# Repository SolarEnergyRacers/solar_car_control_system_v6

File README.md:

# solar_car_control_system_v6

[solarenergyracers.ch](https://www.solarenergyracers.ch) - control system (multi controller based control system for SER v6 solar car)

## Folder Structure

```Text
.
├── AC
│   ├── CMakeLists.txt
│   ├── dependencies.lock
│   ├── lib
│   │   ├── CarControl
│   │   ├── CarState
│   │   ├── CmdHandler
│   │   ├── ConfigReader
│   │   ├── Console
│   │   ├── definitions.h
│   │   ├── Display
│   │   ├── DisplayValue
│   │   ├── DriverDisplay
│   │   ├── EngineerDisplay
│   │   ├── GPIO
│   │   ├── interfaces
│   │   ├── LocalFunctionsAndDevices.h
│   │   ├── OneWireBus
│   │   ├── placeholder.txt
│   │   ├── SDCard
│   │   └── SPIBus
│   ├── platformio.ini
│   ├── sdkconfig
│   ├── sdkconfig.defaults
│   ├── sdkconfig.esp32dev
│   ├── sdkconfig.esp32dev-linux
│   ├── sdkconfig.esp32dev-windows
│   ├── ser_v6_AC.code-workspace
│   ├── src
│   │   ├── CMakeLists.txt
│   │   └── main.cpp
│   └── upload_no_build.py
├── archive_logs.py
├── data
├── datasheets
├── DC
│   ├── CMakeLists.txt
│   ├── dependencies.lock
│   ├── lib
│   │   ├── ADC
│   │   ├── CAN
│   │   ├── CarControl
│   │   ├── CarState
│   │   ├── CmdHandler
│   │   ├── ConstSpeed
│   │   ├── DAC
│   │   ├── definitions.h
│   │   ├── GPIO
│   │   ├── IOExt
│   │   ├── LocalFunctionsAndDevices.h
│   │   ├── OneWireBus
│   │   └── SPIBus
│   ├── platformio.ini
│   ├── sdkconfig
│   ├── sdkconfig.defaults
│   ├── sdkconfig.esp32dev
│   ├── sdkconfig.esp32dev-linux
│   ├── sdkconfig.esp32dev-windows
│   ├── ser_v6_DC.code-workspace
│   ├── src
│   │   ├── CMakeLists.txt
│   │   └── main.cpp
│   └── upload_no_build.py
├── PCBs
│   ├── AuxController
│   ├── ChassisBoard
│   ├── DriveController
│   ├── PDFs_Images
│   └── SwitchBoard
├── docs
├── drafts
├── extras
├── fixes_for_librarys
│   ├── core.h
│   ├── fixes.md
│   └── rtc.h
├── lib_common
│   ├── CAN
│   ├── Console
│   ├── Helper
│   ├── I2CBus
│   ├── include
│   ├── interfaces
│   ├── RTC
│   ├── Serial
│   └── System
├── platformio.txt
├── README.md
├── reset_usb_numbering.py
└── start-vscode-for-AC-DC-workspace.py

```

## Drafts

- 
- 
- 
- 
- 

## Docs

- [Signal Flows](docs/SignalFlows.md)
- [CAN Signal](docs/SignalFlows_CAN-Definitions.md)

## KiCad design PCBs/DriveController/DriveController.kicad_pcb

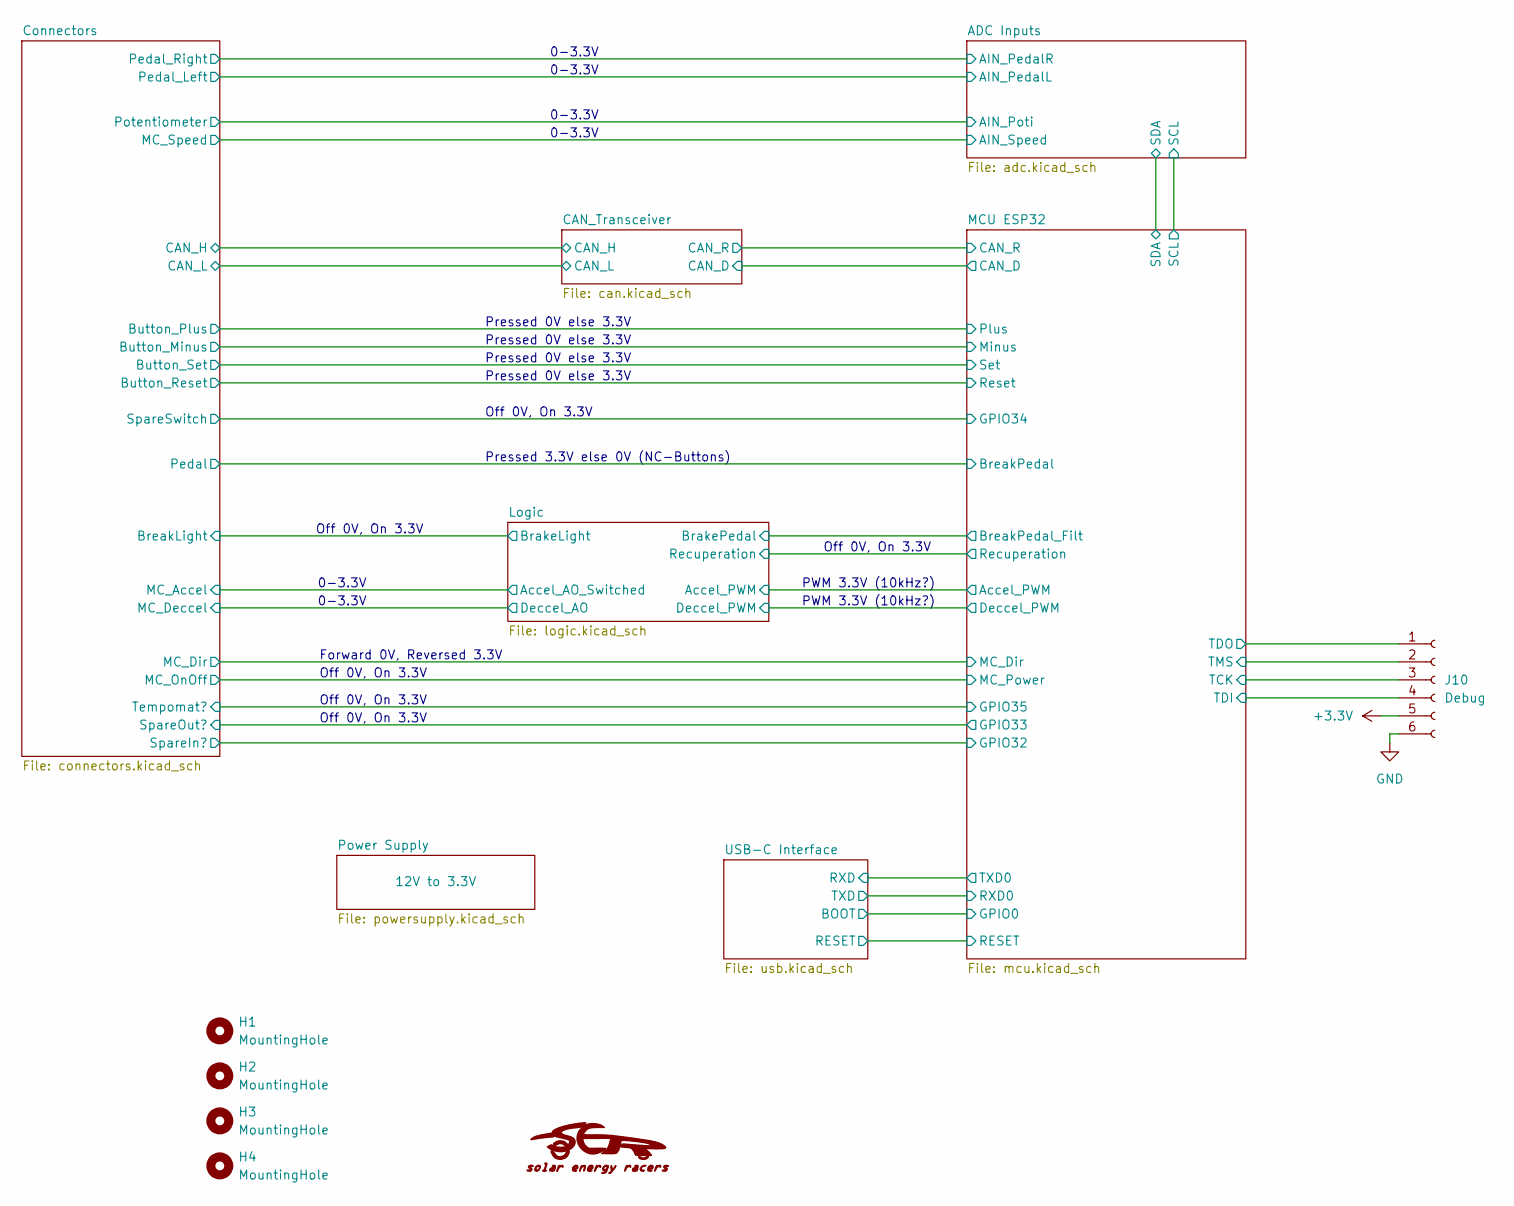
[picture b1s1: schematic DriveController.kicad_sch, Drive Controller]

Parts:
G1: LOGO; SER_Logo
H1, H2, H3, H4: MountingHole; MountingHole_3.2mm_M3_No_Copper
J10: Debug; PinSocket_1x06_P2.54mm_Vertical

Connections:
+3.3V: J10.5; also elsewhere on the board
/MCU ESP32/TCK: J10.3; also elsewhere on the board
/MCU ESP32/TDI: J10.4; also elsewhere on the board
/MCU ESP32/TDO: J10.1; also elsewhere on the board
/MCU ESP32/TMS: J10.2; also elsewhere on the board
GND: J10.6; also elsewhere on the board

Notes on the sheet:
Off 0V, On 3.3V
Forward 0V, Reversed 3.3V
PWM 3.3V (10kHz?)
0-3.3V
Pressed 3.3V else 0V (NC-Buttons)
Pressed 0V else 3.3V

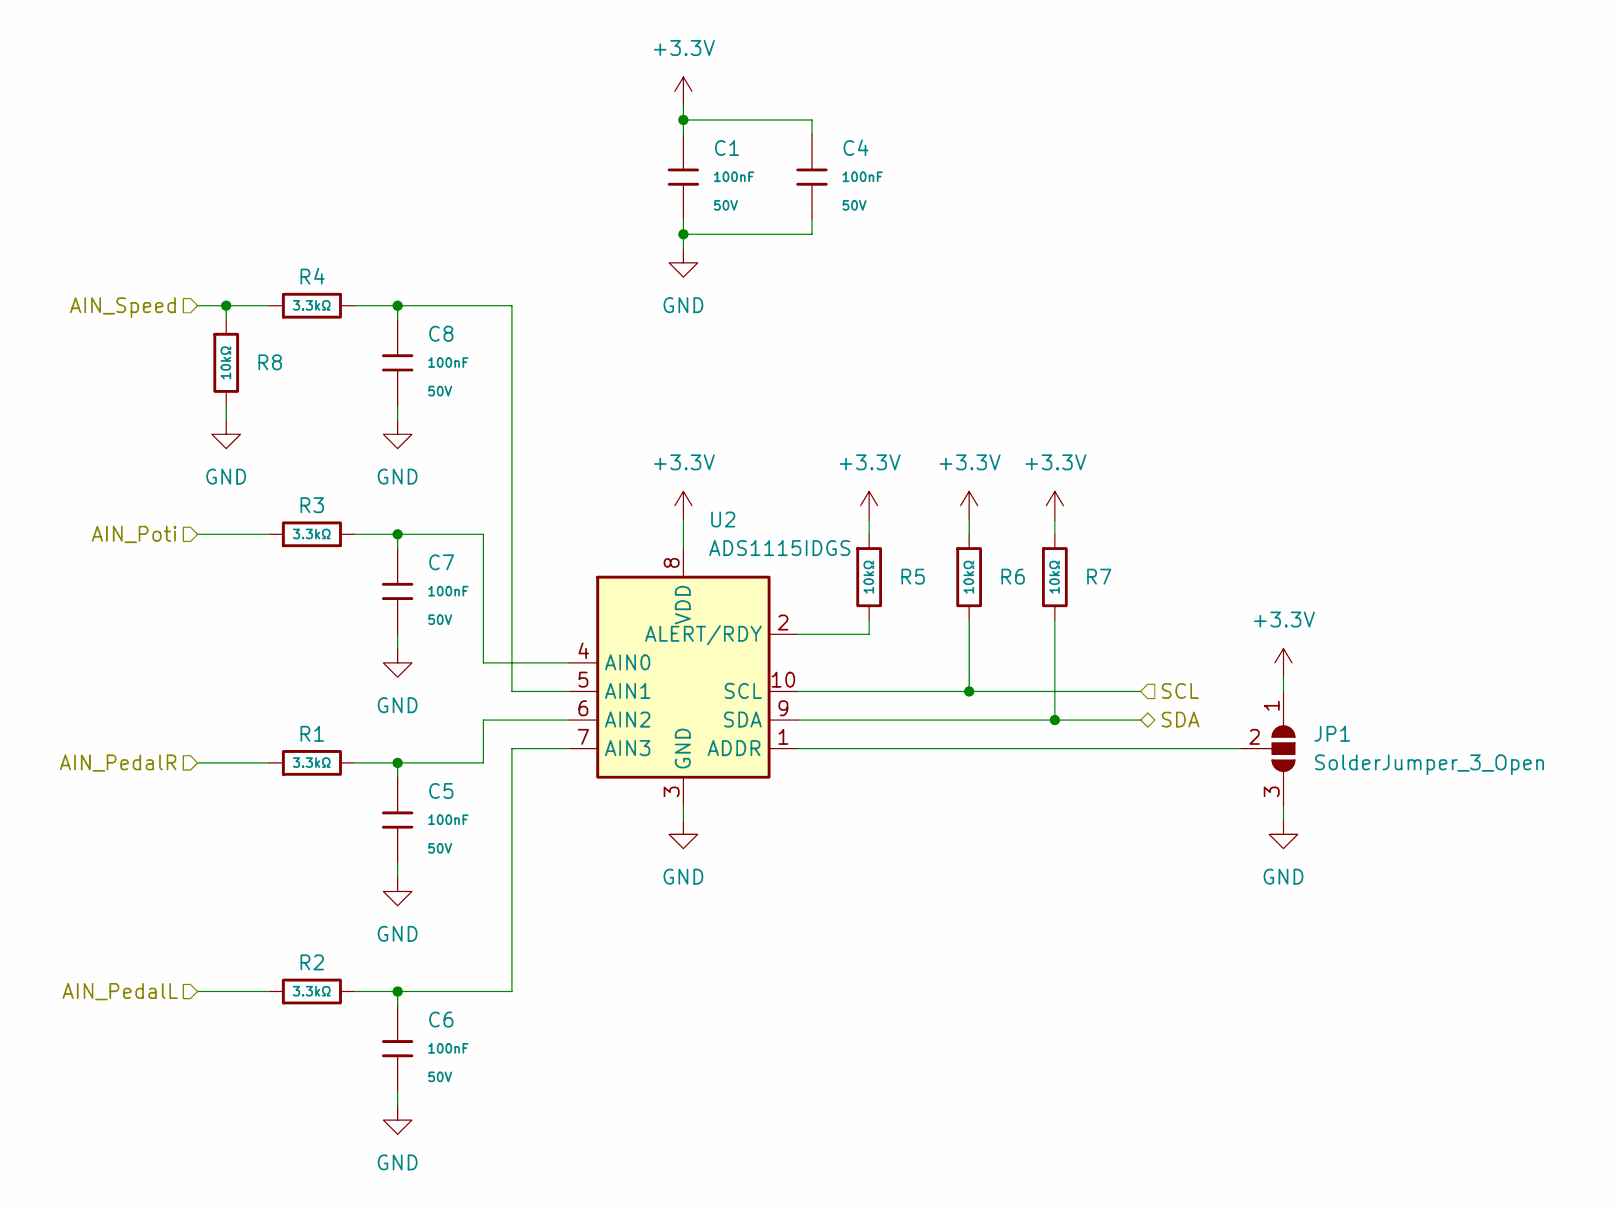
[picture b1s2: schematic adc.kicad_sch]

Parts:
C1, C4, C5, C6, C7, C8: 100nF; C_0603; Voltage Rated 50V; Tolerance ±10%; Part CC0603KRX7R9BB104; LCSC C14663
JP1: SolderJumper_3_Open; SolderJumper-3_P1.3mm_Open_Pad1.0x1.5mm_NumberLabels
R1, R2, R3, R4: 3.3kΩ; R_0603; Overload Voltage (Max) 75V; Tolerance ±1%; Part 0603WAF3301T5E; LCSC C22978
R5, R6, R7, R8: 10kΩ; R_0603; Overload Voltage (Max) 75V; Tolerance ±1%; Part 0603WAF1002T5E; LCSC C25804
U2: ADS1115IDGS; TSSOP-10_3x3mm_P0.5mm

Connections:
+3.3V: C1.1, C4.1, JP1.1 (A), R5.1, R6.1, R7.1, U2.8 (VDD); also elsewhere on the board
/ADC Inputs/AIN_PedalL: R2.1; also elsewhere on the board
/ADC Inputs/AIN_PedalR: R1.1; also elsewhere on the board
/ADC Inputs/AIN_Poti: R3.1; also elsewhere on the board
/ADC Inputs/AIN_Speed: R4.1, R8.1; also elsewhere on the board
/ADC Inputs/SCL: R6.2, U2.10 (SCL); also elsewhere on the board
/ADC Inputs/SDA: R7.2, U2.9 (SDA); also elsewhere on the board
GND: C1.2, C4.2, C5.2, C6.2, C7.2, C8.2, JP1.3 (B), R8.2, U2.3 (GND); also elsewhere on the board
unnamed: JP1.2 (C), U2.1 (ADDR)
unnamed: C7.1, R3.2, U2.4 (AIN0)
unnamed: C8.1, R4.2, U2.5 (AIN1)
unnamed: C5.1, R1.2, U2.6 (AIN2)
unnamed: C6.1, R2.2, U2.7 (AIN3)
unnamed: R5.2, U2.2 (ALERT/RDY)

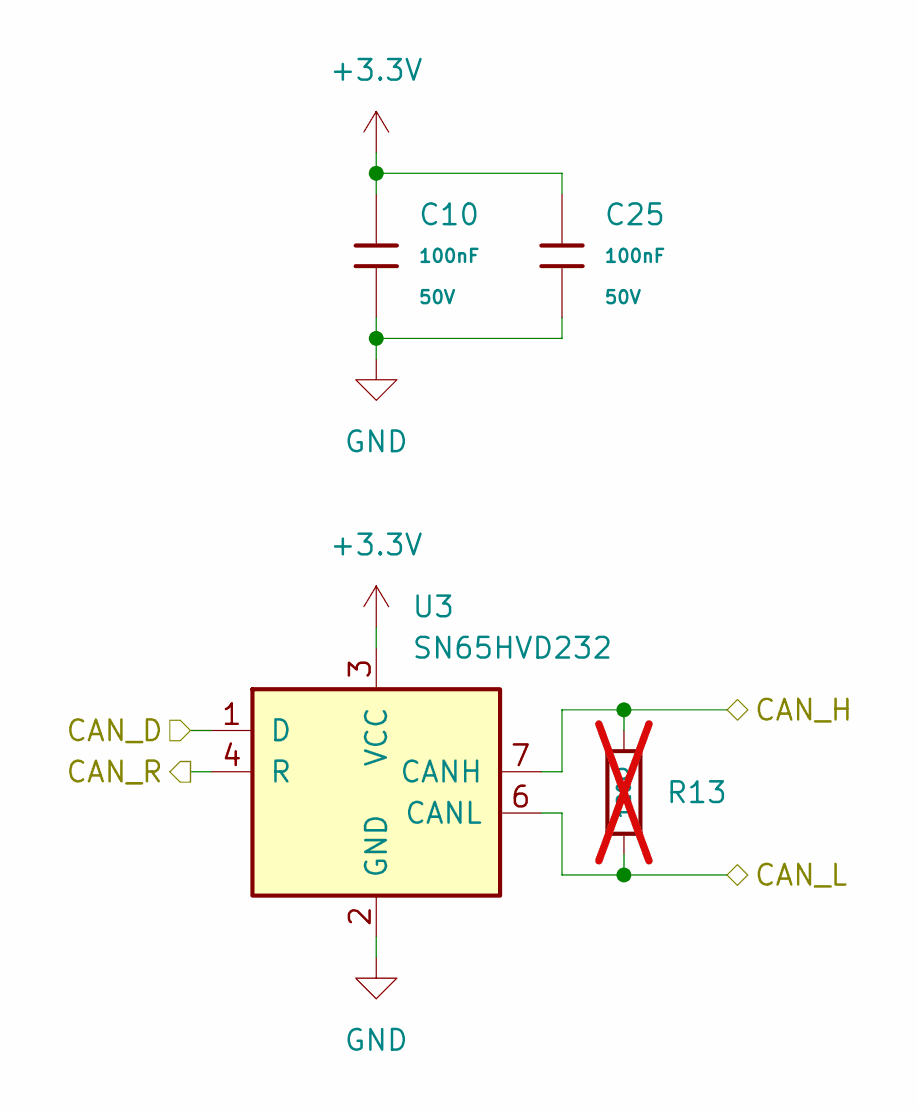
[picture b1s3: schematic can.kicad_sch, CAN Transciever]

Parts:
C10, C25: 100nF; C_0603; Voltage Rated 50V; Tolerance ±10%; Part CC0603KRX7R9BB104; LCSC C14663
R13: 120Ω; R_0603; Overload Voltage (Max) 75V; Tolerance ±1%; Part 0603WAF1200T5E; LCSC C22787; not fitted
U3: SN65HVD232; SOIC-8_3.9x4.9mm_P1.27mm

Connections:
+3.3V: C10.1, C25.1, U3.3 (VCC); also elsewhere on the board
/CAN_Transceiver/CAN_D: U3.1 (D); also elsewhere on the board
/CAN_Transceiver/CAN_H: R13.1, U3.7 (CANH); also elsewhere on the board
/CAN_Transceiver/CAN_L: R13.2, U3.6 (CANL); also elsewhere on the board
/CAN_Transceiver/CAN_R: U3.4 (R); also elsewhere on the board
GND: C10.2, C25.2, U3.2 (GND); also elsewhere on the board

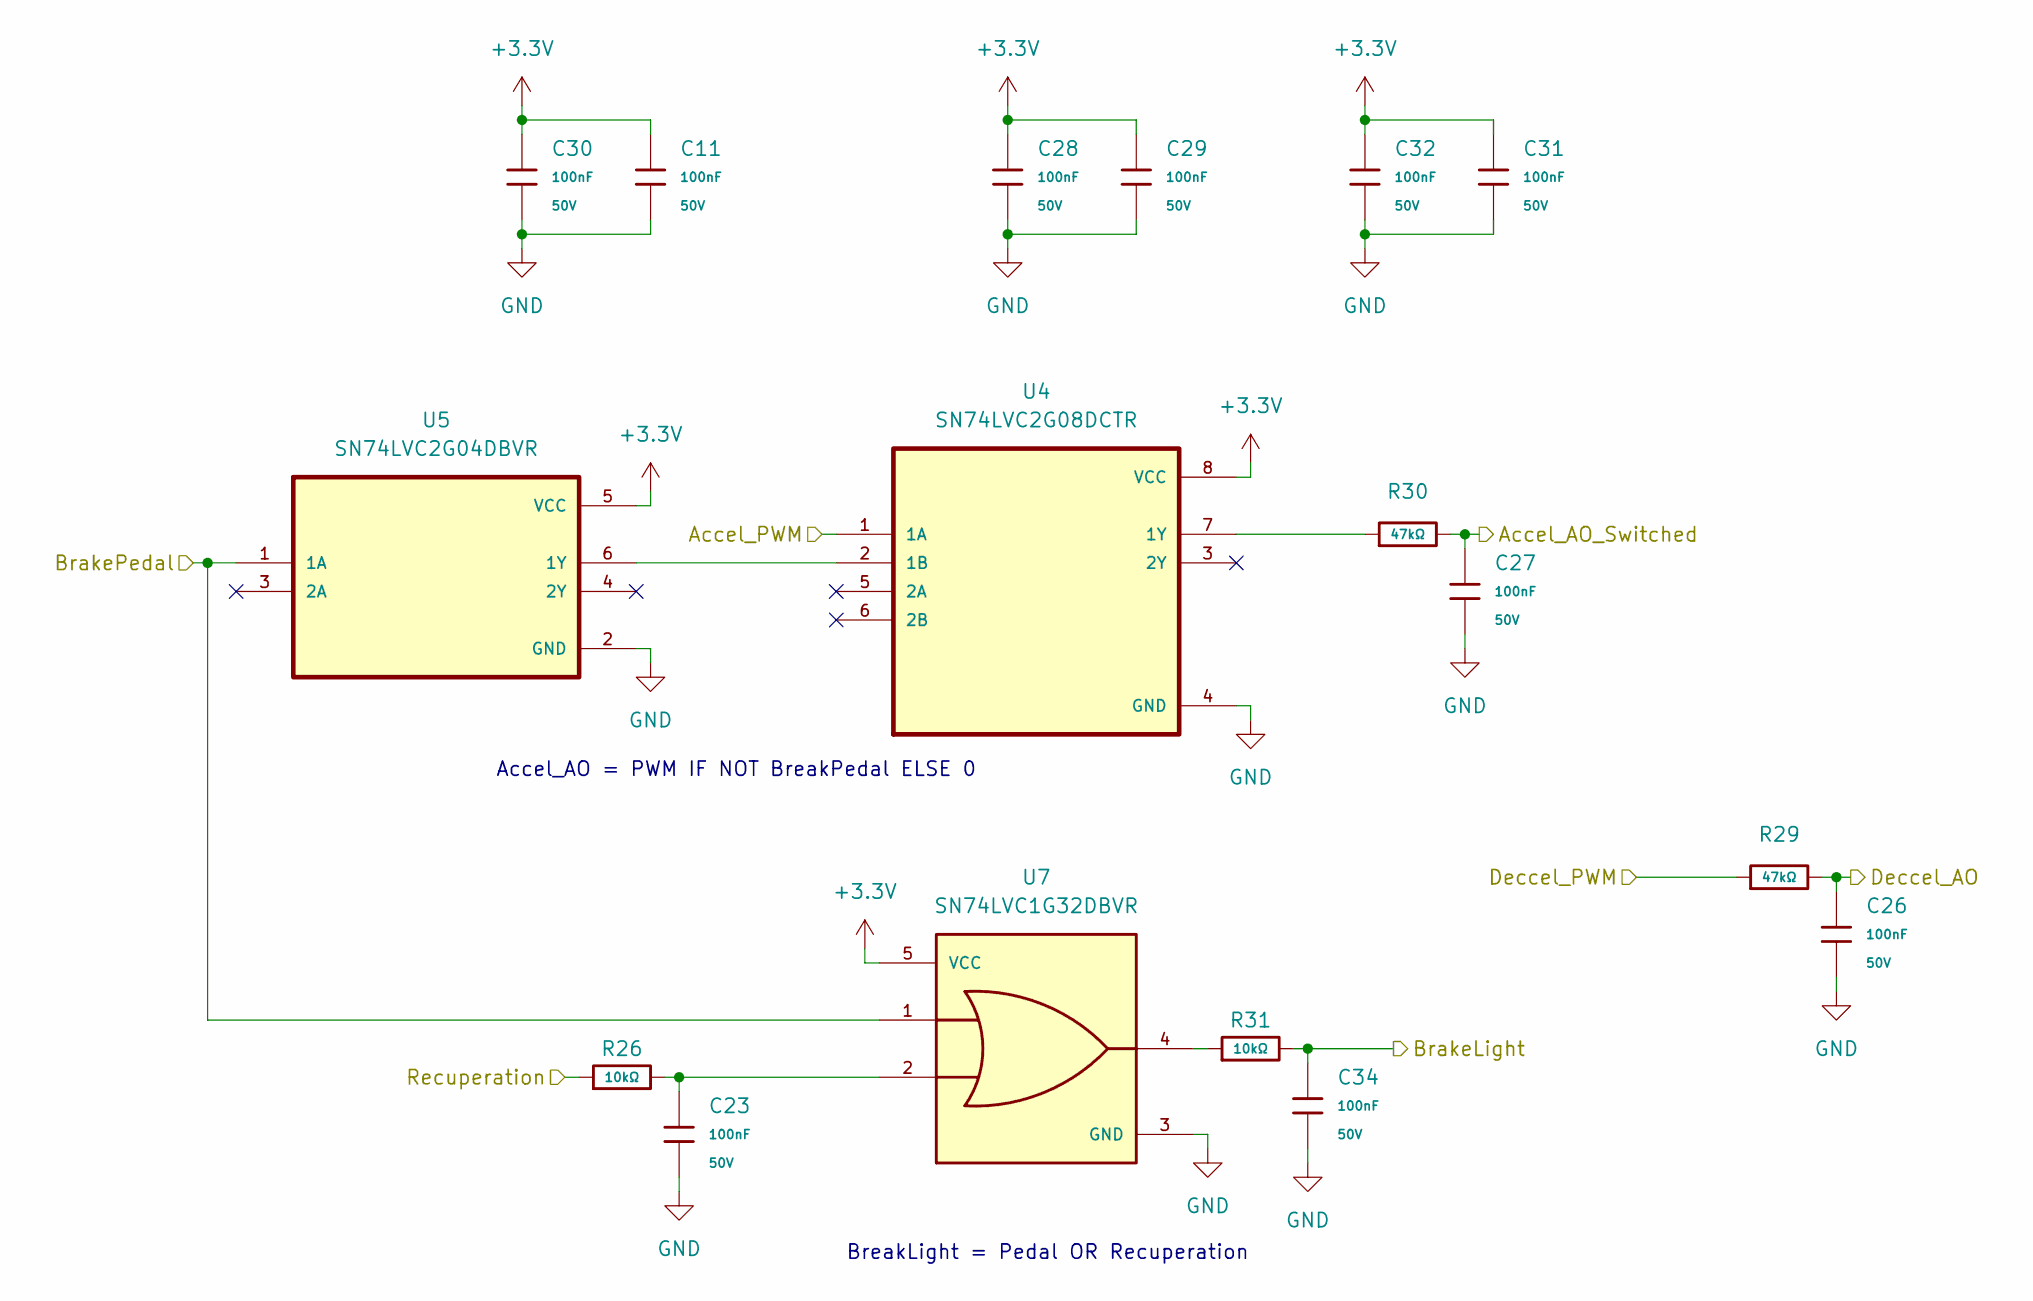
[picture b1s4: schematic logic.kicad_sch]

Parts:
C11, C23, C26, C27, C28, C29, C30, C31, C32, C34: 100nF; C_0603; Voltage Rated 50V; Tolerance ±10%; Part CC0603KRX7R9BB104; LCSC C14663
R26, R31: 10kΩ; R_0603; Overload Voltage (Max) 75V; Tolerance ±1%; Part 0603WAF1002T5E; LCSC C25804
R29, R30: 47kΩ; R_0603; Overload Voltage (Max) 75V; Tolerance ±1%; Part 0603WAF4702T5E; LCSC C25819
U4: SN74LVC2G08DCTR; VSSOP-8_2.3x2mm_P0.5mm_modified
U5: SN74LVC2G04DBVR; SOT-23-6
U7: SN74LVC1G32DBVR; SOT-23-5; PARTREV V

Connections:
+3.3V: C11.1, C28.1, C29.1, C30.1, C31.1, C32.1, U4.8 (VCC), U5.5 (VCC), U7.5 (VCC); also elsewhere on the board
/Connectors/BreakLight: C34.1, R31.2; also elsewhere on the board
/Connectors/MC_Accel: C27.1, R30.2; also elsewhere on the board
/Connectors/MC_Deccel: C26.1, R29.2; also elsewhere on the board
/Logic/Accel_PWM: U4.1 (1A); also elsewhere on the board
/Logic/BrakePedal: U5.1 (1A), U7.1; also elsewhere on the board
/Logic/Deccel_PWM: R29.1; also elsewhere on the board
/Logic/Recuperation: R26.1; also elsewhere on the board
GND: C11.2, C23.2, C26.2, C27.2, C28.2, C29.2, C30.2, C31.2, C32.2, C34.2, U4.4 (GND), U5.2 (GND), U7.3 (GND); also elsewhere on the board
unnamed: C23.1, R26.2, U7.2
unnamed: R31.1, U7.4
unnamed: U4.2 (1B), U5.6 (1Y)
unnamed: R30.1, U4.7 (1Y)

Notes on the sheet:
BreakLight = Pedal OR Recuperation
Accel_AO = PWM IF NOT BreakPedal ELSE 0

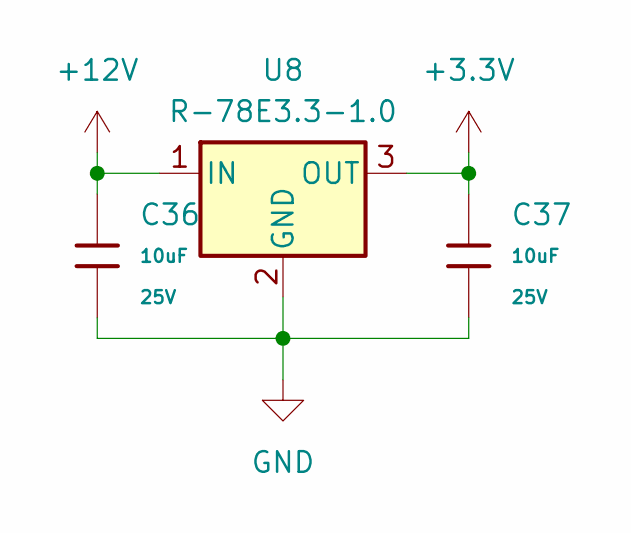
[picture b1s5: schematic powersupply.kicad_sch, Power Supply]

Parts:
C36, C37: 10uF; C_0805; Voltage Rated 25V; Tolerance ±10%; Part CL21A106KAYNNNE; LCSC C15850
U8: R-78E3.3-1.0; Converter_DCDC_RECOM_R-78E-0.5_THT

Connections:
+3.3V: C37.1, U8.3 (OUT); also elsewhere on the board
+12V: C36.1, U8.1 (IN); also elsewhere on the board
GND: C36.2, C37.2, U8.2 (GND); also elsewhere on the board

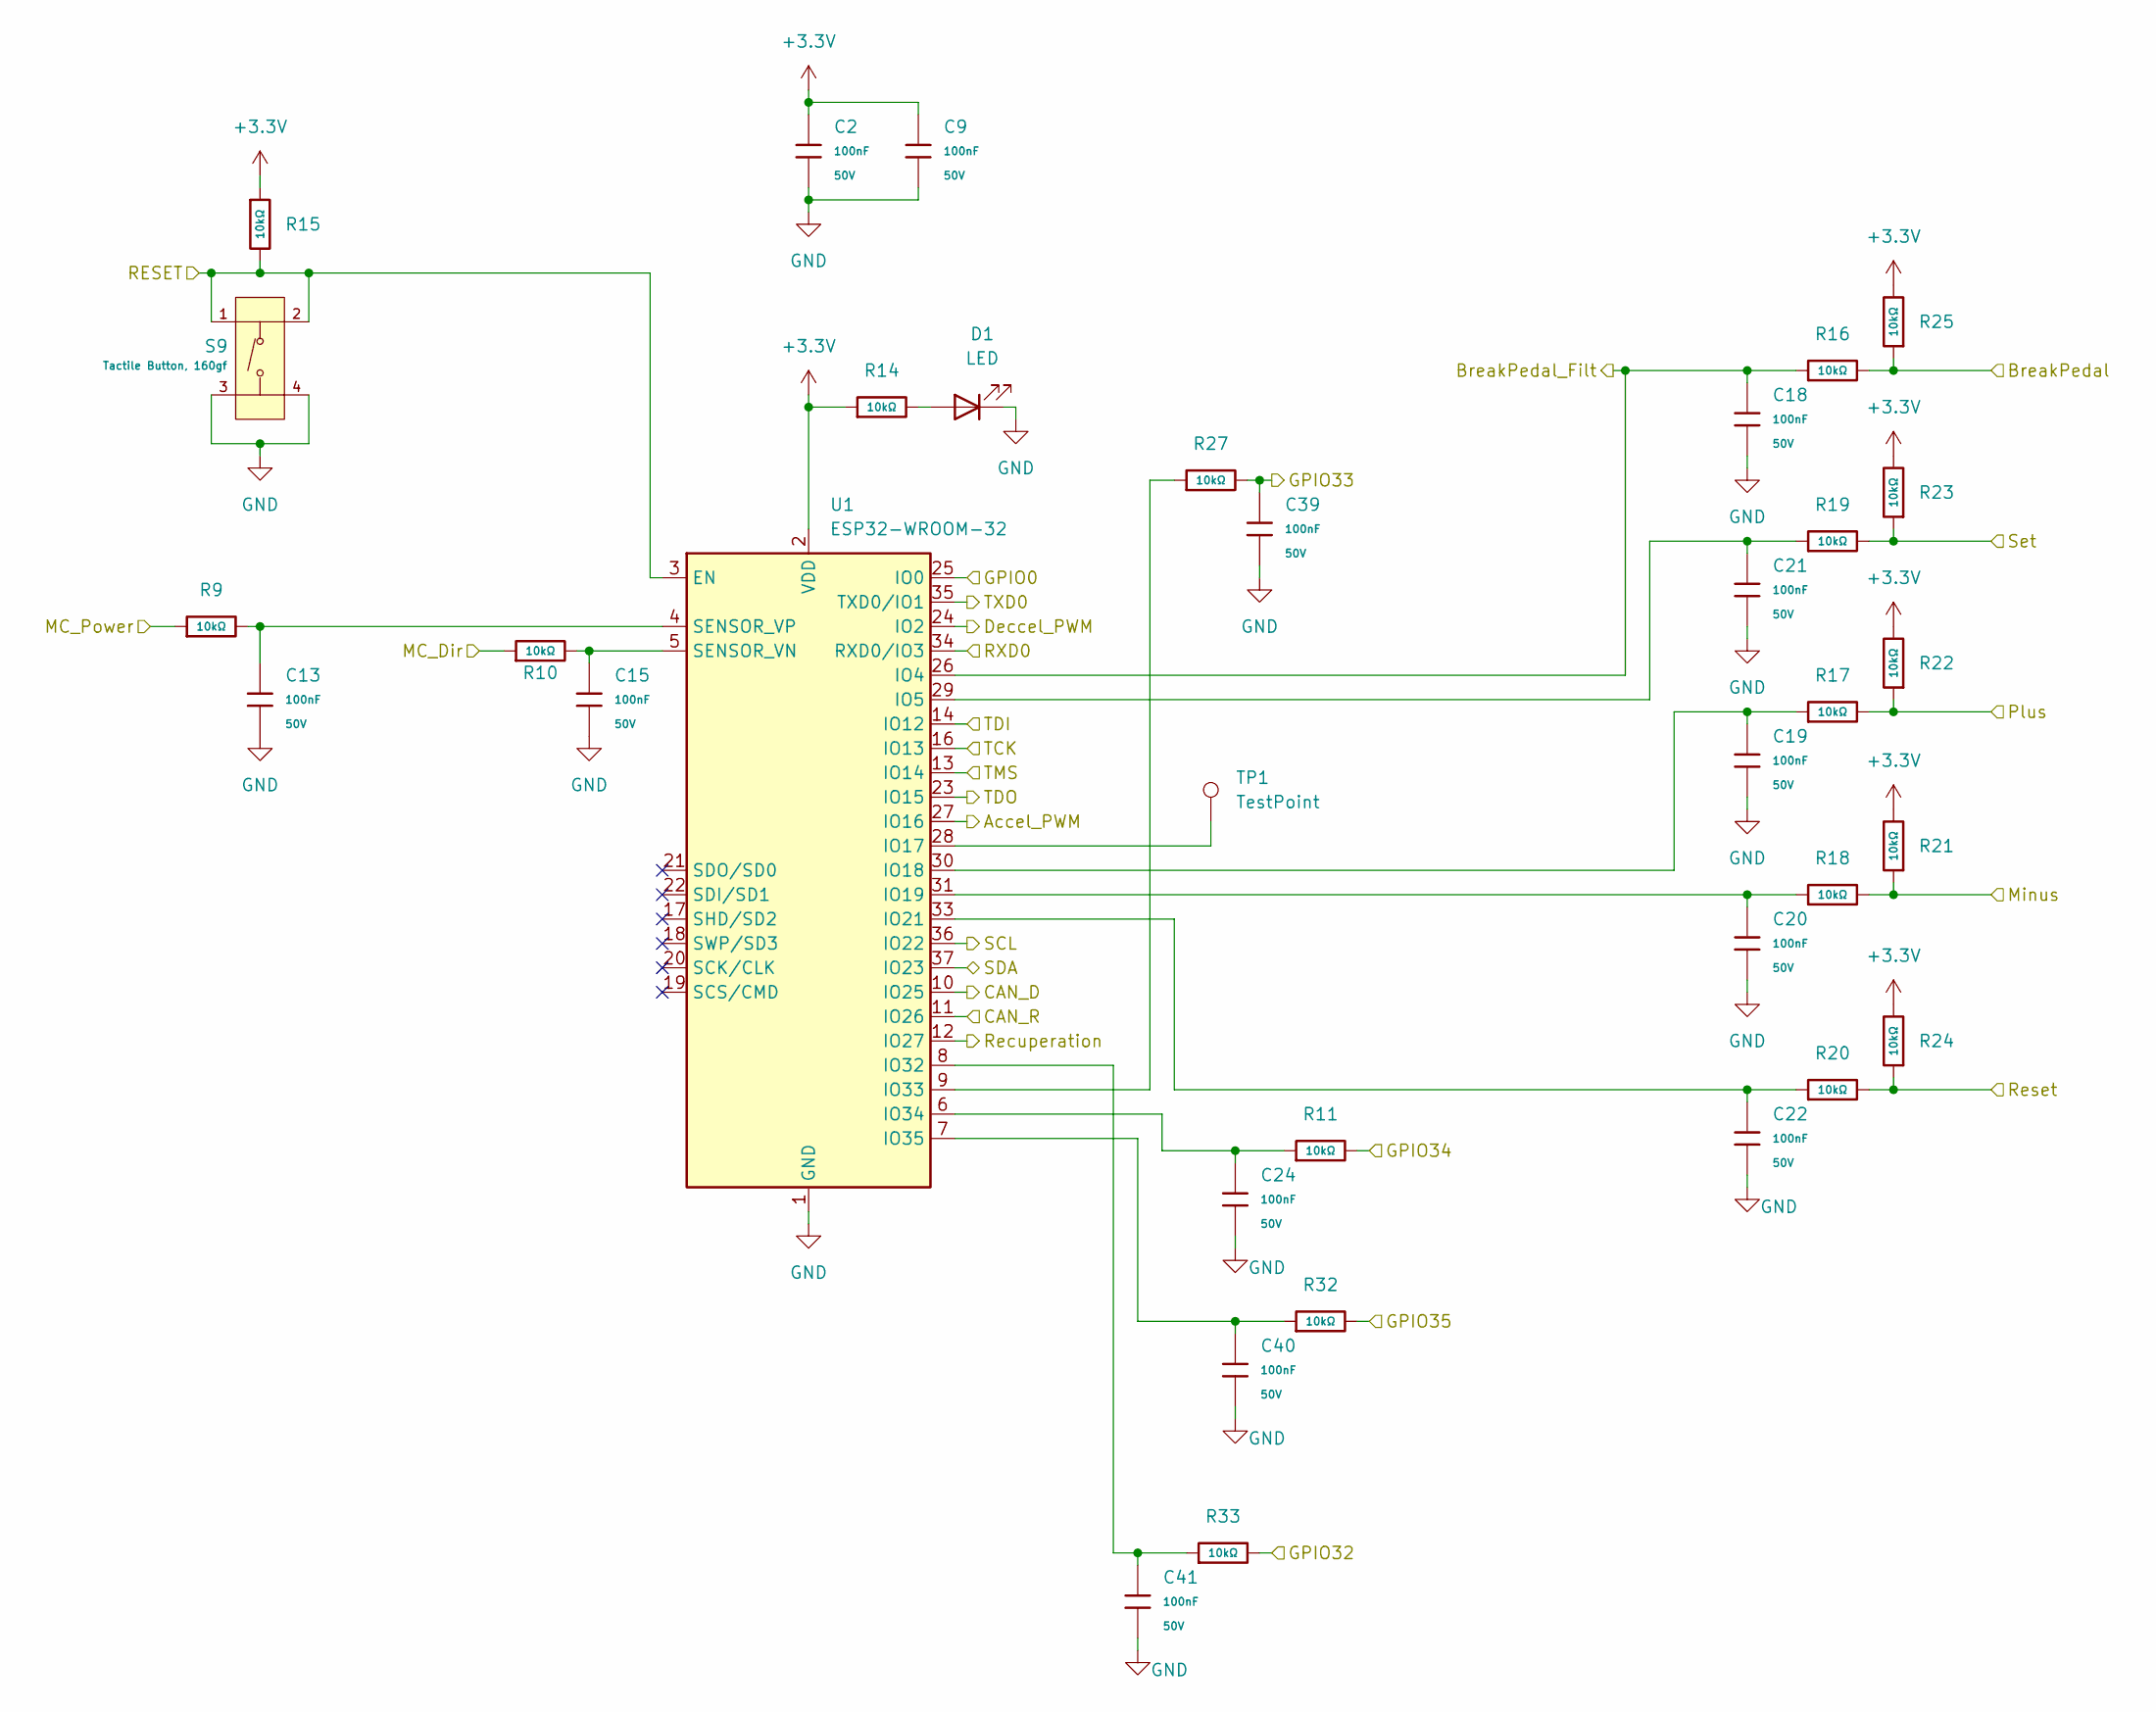
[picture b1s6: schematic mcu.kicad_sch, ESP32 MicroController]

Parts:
C2, C9, C13, C15, C18, C19, C20, C21, C22, C24, C39, C40, C41: 100nF; C_0603; Voltage Rated 50V; Tolerance ±10%; Part CC0603KRX7R9BB104; LCSC C14663
D1: LED; LED_0603_1608Metric
R9, R10, R11, R14, R15, R16, R17, R18, R19, R20, R21, R22, R23, R24, R25, R27, R32, R33: 10kΩ; R_0603; Overload Voltage (Max) 75V; Tolerance ±1%; Part 0603WAF1002T5E; LCSC C25804
S9: Tactile Button, 160gf; SW-SMD_4P-L5.1-W5.1-P3.70-LS6.5-TL-2; Voltage Rating (Dc) 12V; Part TS-1187A-B-A-B; LCSC C318884
TP1: TestPoint; TestPoint_Pad_1.0x1.0mm
U1: ESP32-WROOM-32

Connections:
+3.3V: C2.1, C9.1, R14.1, R15.1, R21.2, R22.2, R23.2, R24.2, R25.2, U1.2 (VDD); also elsewhere on the board
/ADC Inputs/SCL: U1.36 (IO22); also elsewhere on the board
/ADC Inputs/SDA: U1.37 (IO23); also elsewhere on the board
/CAN_Transceiver/CAN_D: U1.10 (IO25); also elsewhere on the board
/CAN_Transceiver/CAN_R: U1.11 (IO26); also elsewhere on the board
/Connectors/Button_Minus: R18.2, R21.1; also elsewhere on the board
/Connectors/Button_Plus: R17.2, R22.1; also elsewhere on the board
/Connectors/Button_Reset: R20.2, R24.1; also elsewhere on the board
/Connectors/Button_Set: R19.2, R23.1; also elsewhere on the board
/Connectors/MC_Dir: R10.1; also elsewhere on the board
/Connectors/MC_OnOff: R9.1; also elsewhere on the board
/Connectors/Pedal: R16.2, R25.1; also elsewhere on the board
/Connectors/SpareIn?: R33.2; also elsewhere on the board
/Connectors/SpareOut?: C39.1, R27.2; also elsewhere on the board
/Connectors/SpareSwitch: R11.2; also elsewhere on the board
/Connectors/Tempomat?: R32.2; also elsewhere on the board
/Logic/Accel_PWM: U1.27 (IO16); also elsewhere on the board
/Logic/BrakePedal: C18.1, R16.1, U1.26 (IO4); also elsewhere on the board
/Logic/Deccel_PWM: U1.24 (IO2); also elsewhere on the board
/Logic/Recuperation: U1.12 (IO27); also elsewhere on the board
/MCU ESP32/GPIO0: U1.25 (IO0); also elsewhere on the board
/MCU ESP32/RESET: R15.2, S9.1 (A), S9.2 (B), U1.3 (EN); also elsewhere on the board
/MCU ESP32/RXD0: U1.34 (RXD0/IO3); also elsewhere on the board
/MCU ESP32/TCK: U1.16 (IO13); also elsewhere on the board
/MCU ESP32/TDI: U1.14 (IO12); also elsewhere on the board
/MCU ESP32/TDO: U1.23 (IO15); also elsewhere on the board
/MCU ESP32/TMS: U1.13 (IO14); also elsewhere on the board
/MCU ESP32/TXD0: U1.35 (TXD0/IO1); also elsewhere on the board
GND: C2.2, C9.2, C13.2, C15.2, C18.2, C19.2, C20.2, C21.2, C22.2, C24.2, C39.2, C40.2, C41.2, D1.1 (K), S9.3 (C), S9.4 (D), U1.1 (GND), U1.15 (GND), U1.38 (GND), U1.39 (GND); also elsewhere on the board
unnamed: D1.2 (A), R14.2
unnamed: C21.1, R19.1, U1.29 (IO5)
unnamed: TP1.1, U1.28 (IO17)
unnamed: C19.1, R17.1, U1.30 (IO18)
unnamed: C20.1, R18.1, U1.31 (IO19)
unnamed: C22.1, R20.1, U1.33 (IO21)
unnamed: C41.1, R33.1, U1.8 (IO32)
unnamed: R27.1, U1.9 (IO33)
unnamed: C24.1, R11.1, U1.6 (IO34)
unnamed: C40.1, R32.1, U1.7 (IO35)
unnamed: C15.1, R10.2, U1.5 (SENSOR_VN)
unnamed: C13.1, R9.2, U1.4 (SENSOR_VP)

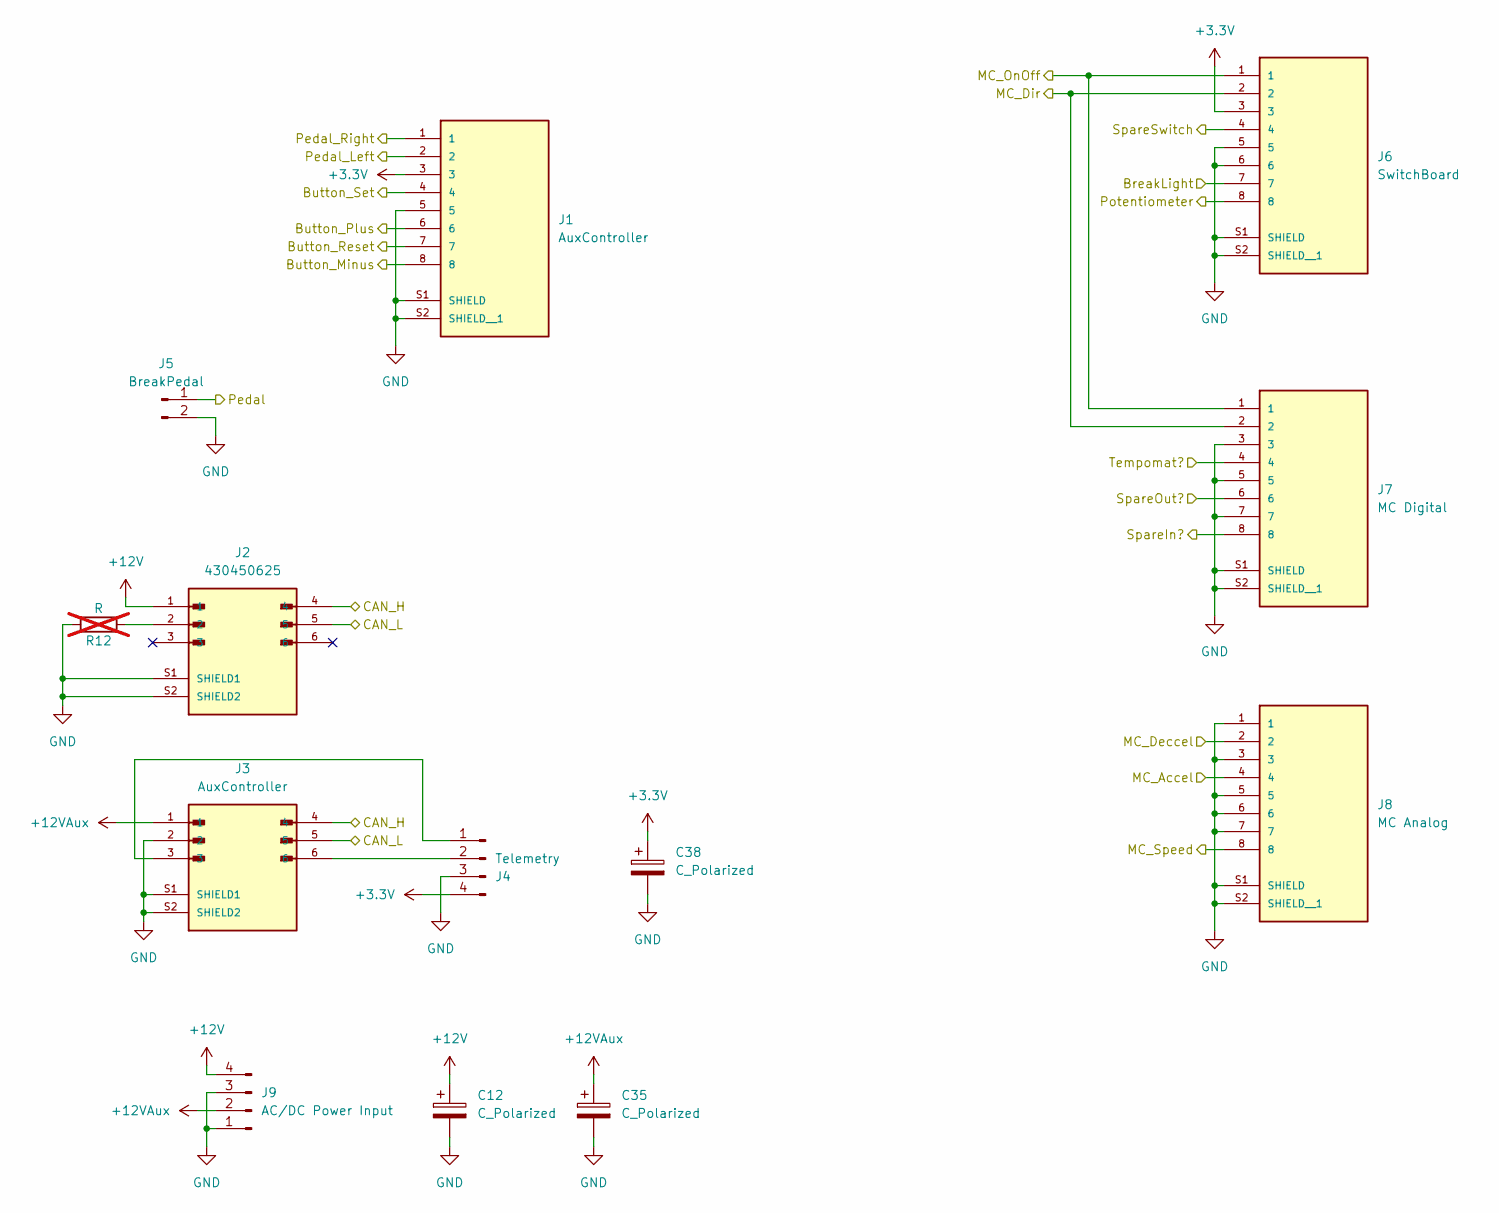
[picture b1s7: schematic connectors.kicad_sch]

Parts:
C12, C35, C38: C_Polarized; CP_Radial_D8.0mm_P5.00mm
J1: AuxController; CUI_CRJ027-1-TH; PARTREV 1.0
J2: 430450625; MOLEX_430450625; PARTREV H4
J3: AuxController; MOLEX_430450625; PARTREV H4
J4: Telemetry; PhoenixContact_MCV_1,5_4-G-3.5_1x04_P3.50mm_Vertical
J5: BreakPedal; PhoenixContact_MCV_1,5_2-G-3.5_1x02_P3.50mm_Vertical
J6: SwitchBoard; CUI_CRJ027-1-TH; PARTREV 1.0
J7: MC Digital; CUI_CRJ027-1-TH; PARTREV 1.0
J8: MC Analog; CUI_CRJ027-1-TH; PARTREV 1.0
J9: AC/DC Power Input; PhoenixContact_MCV_1,5_4-G-3.5_1x04_P3.50mm_Vertical
R12: R; R_1206_3216Metric; not fitted

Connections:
+3.3V: C38.1, J1.3, J4.4, J6.3; also elsewhere on the board
+12V: C12.1, J2.1, J9.4; also elsewhere on the board
+12VAux: C35.1, J3.1, J9.2
/ADC Inputs/AIN_PedalL: J1.2; also elsewhere on the board
/ADC Inputs/AIN_PedalR: J1.1; also elsewhere on the board
/ADC Inputs/AIN_Poti: J6.8; also elsewhere on the board
/ADC Inputs/AIN_Speed: J8.8; also elsewhere on the board
/CAN_Transceiver/CAN_H: J2.4, J3.4; also elsewhere on the board
/CAN_Transceiver/CAN_L: J2.5, J3.5; also elsewhere on the board
/Connectors/BreakLight: J6.7; also elsewhere on the board
/Connectors/Button_Minus: J1.8; also elsewhere on the board
/Connectors/Button_Plus: J1.6; also elsewhere on the board
/Connectors/Button_Reset: J1.7; also elsewhere on the board
/Connectors/Button_Set: J1.4; also elsewhere on the board
/Connectors/MC_Accel: J8.4; also elsewhere on the board
/Connectors/MC_Deccel: J8.2; also elsewhere on the board
/Connectors/MC_Dir: J6.2, J7.2; also elsewhere on the board
/Connectors/MC_OnOff: J6.1, J7.1; also elsewhere on the board
/Connectors/Pedal: J5.1; also elsewhere on the board
/Connectors/SpareIn?: J7.8; also elsewhere on the board
/Connectors/SpareOut?: J7.6; also elsewhere on the board
/Connectors/SpareSwitch: J6.4; also elsewhere on the board
/Connectors/Tempomat?: J7.4; also elsewhere on the board
GND: C12.2, C35.2, C38.2, J1.5, J1.S1 (SHIELD), J1.S2 (SHIELD__1), J2.S1 (SHIELD1), J2.S2 (SHIELD2), J3.2, J3.S1 (SHIELD1), J3.S2 (SHIELD2), J4.3, J5.2, J6.5, J6.6, J6.S1 (SHIELD), J6.S2 (SHIELD__1), J7.3, J7.5, J7.7, J7.S1 (SHIELD), J7.S2 (SHIELD__1), J8.1, J8.3, J8.5, J8.6, J8.7, J8.S1 (SHIELD), J8.S2 (SHIELD__1), J9.1, J9.3, R12.2; also elsewhere on the board
unnamed: J2.2, R12.1
unnamed: J3.3, J4.1
unnamed: J3.6, J4.2

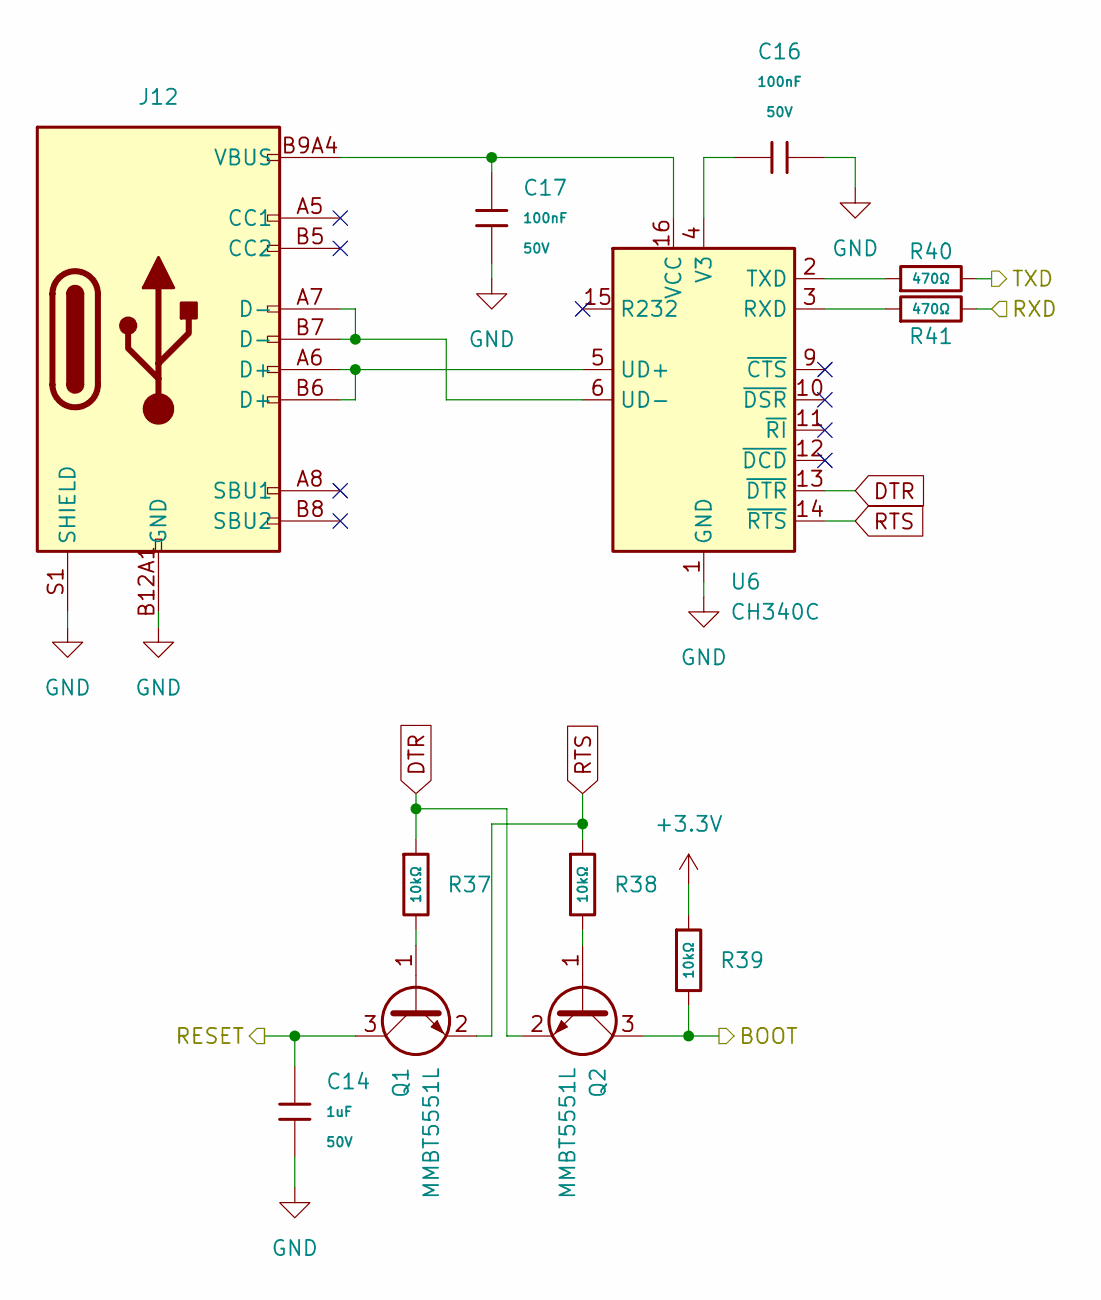
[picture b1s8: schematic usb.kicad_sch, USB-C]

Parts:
C14: 1uF; C_0603; Voltage Rated 50V; Tolerance ±10%; Part CL10A105KB8NNNC; LCSC C15849
C16, C17: 100nF; C_0603; Voltage Rated 50V; Tolerance ±10%; Part CC0603KRX7R9BB104; LCSC C14663
J12: Connector, USB-TYPE-C-16P; TYPE-C-SMD_HX-TYPE-C-16PIN; LCSC C2927039
Q1, Q2: MMBT5551L; SOT-23
R37, R38, R39: 10kΩ; R_0603; Overload Voltage (Max) 75V; Tolerance ±1%; Part 0603WAF1002T5E; LCSC C25804
R40, R41: 470Ω; R_0603; Overload Voltage (Max) 75V; Tolerance ±1%; Part 0603WAF4700T5E; LCSC C23179
U6: CH340C; SOIC-16_3.9x9.9mm_P1.27mm

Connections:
+3.3V: R39.1; also elsewhere on the board
/MCU ESP32/GPIO0: Q2.3 (C), R39.2; also elsewhere on the board
/MCU ESP32/RESET: C14.1, Q1.3 (C); also elsewhere on the board
/MCU ESP32/RXD0: R40.2; also elsewhere on the board
/MCU ESP32/TXD0: R41.2; also elsewhere on the board
DTR: Q2.2 (E), R37.1, U6.13 (~DTR)
GND: C14.2, C16.2, C17.1, J12.A12B1 (GND), J12.B12A1 (GND), J12.S1 (SHIELD), U6.1 (GND); also elsewhere on the board
unnamed: Q1.1 (B), R37.2
unnamed: Q2.1 (B), R38.2
unnamed: R41.1, U6.3 (RXD)
unnamed: R40.1, U6.2 (TXD)
unnamed: J12.A6 (D+), J12.B6 (D+), U6.5 (UD+)
unnamed: J12.A7 (D-), J12.B7 (D-), U6.6 (UD-)
unnamed: C16.1, U6.4 (V3)
unnamed: C17.2, J12.A9B4 (VBUS), J12.B9A4 (VBUS), U6.16 (VCC)
RTS: Q1.2 (E), R38.1, U6.14 (~RTS)
